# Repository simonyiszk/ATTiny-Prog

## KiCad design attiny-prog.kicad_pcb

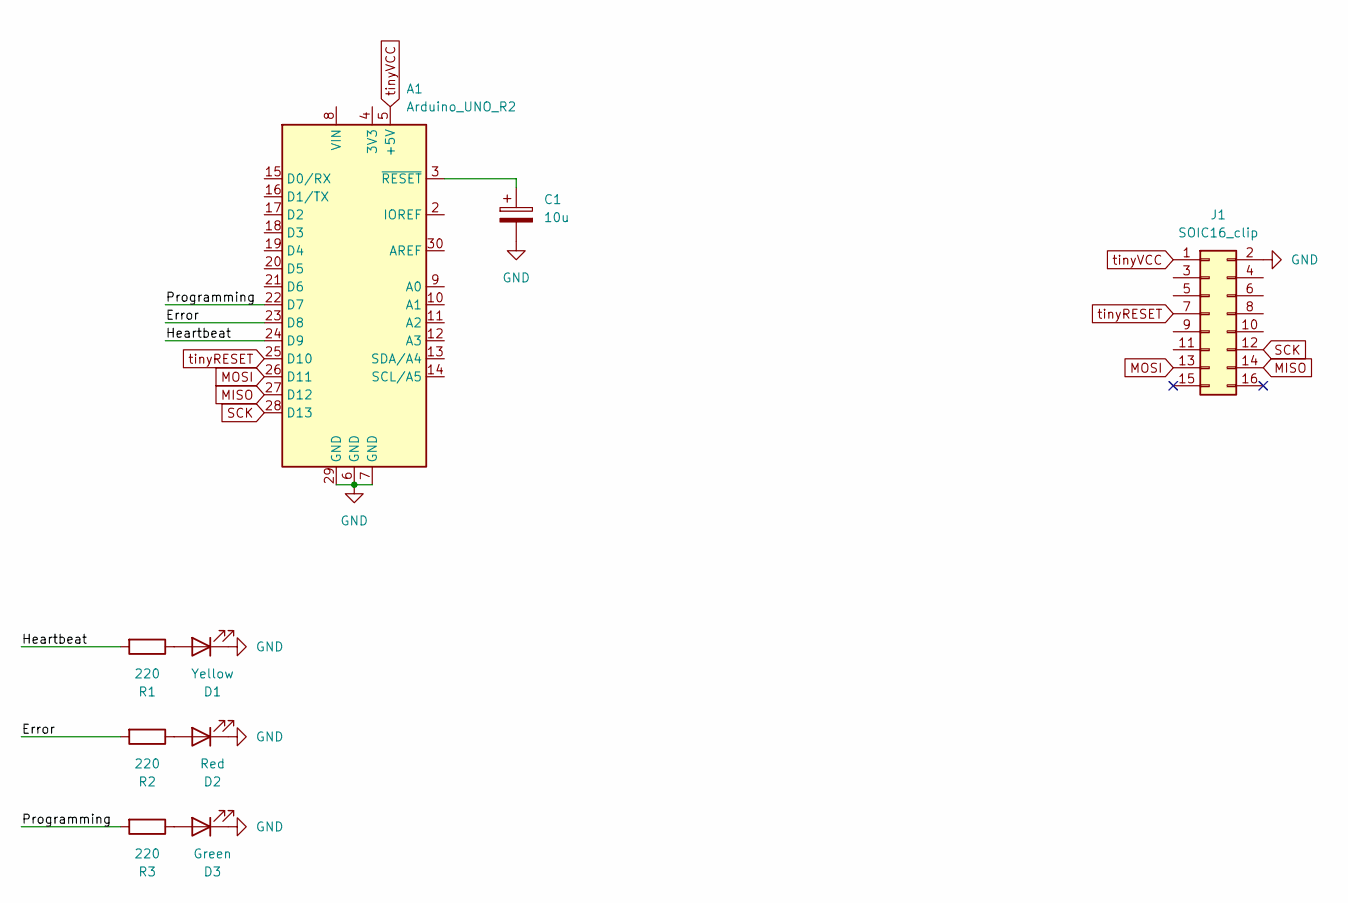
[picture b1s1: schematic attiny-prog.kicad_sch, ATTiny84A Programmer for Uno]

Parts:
A1: Arduino_UNO_R2
C1: 10u; CP_Elec_5x5.8
D1: Yellow; LED_0805_2012Metric
D2: Red; LED_0805_2012Metric
D3: Green; LED_0805_2012Metric
J1: SOIC16_clip; PinHeader_2x08_P2.54mm_Vertical_SMD
R1, R2, R3: 220; R_0805_2012Metric

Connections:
/Error: A1.23 (D8), R2.2
/Heartbeat: A1.24 (D9), R1.2
/Programming: A1.22 (D7), R3.2
GND: A1.6 (GND), A1.7 (GND), A1.29 (GND), C1.2, D1.1 (K), D2.1 (K), D3.1 (K), J1.2
MISO: A1.27 (D12), J1.14
MOSI: A1.26 (D11), J1.13
unnamed: A1.3 (~RESET), C1.1
unnamed: D1.2 (A), R1.1
unnamed: D2.2 (A), R2.1
unnamed: D3.2 (A), R3.1
SCK: A1.28 (D13), J1.12
tinyRESET: A1.25 (D10), J1.7
tinyVCC: A1.5 (+5V), J1.1

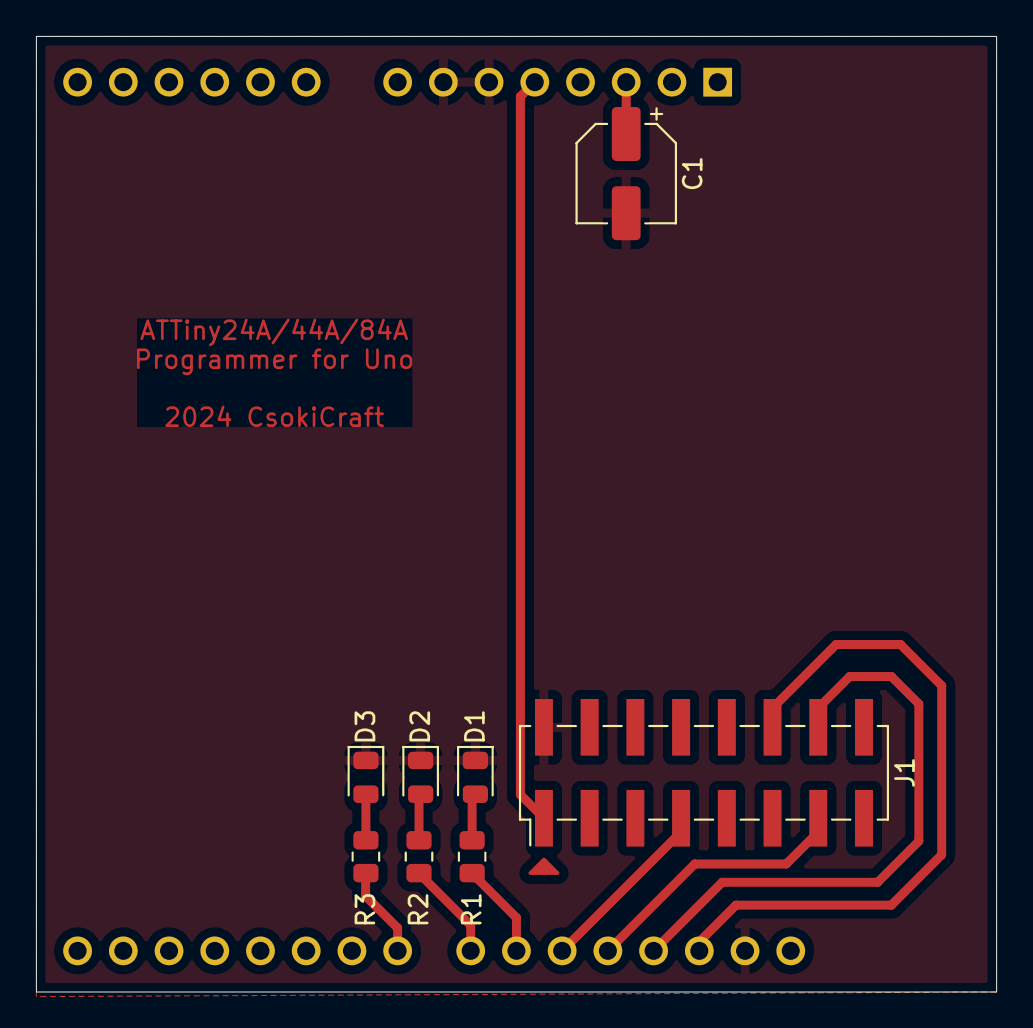
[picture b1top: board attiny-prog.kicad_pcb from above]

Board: 2 copper layers, 53.3 x 53.1 mm, 9 parts (1 on the bottom side), 13 nets.

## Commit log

2024-12-12 First revision
2024-12-12 Second revision
    * fixed SOIC_clip header pinout
    * added reset capacitor value
